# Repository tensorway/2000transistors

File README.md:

# 2000 MOSFET processor

The project is made in Kicad. If you want to learn more about it visit [howcpuworks.com](howcpuworks.com).

## Conventions
- all transistors on a board point into the same direction (or 2 perpendicular ones if needed)
- all leds point into the same direction
- 1k resistors are labeled with white rectangle, 1M with empty one (only violation is in the Clock board and two voltage divider resistors in LCD board)
- "*" means high significance bits
- "+" means positive 5V

## Tips
- you dont need to use extra usb for the power, powering through arduino is enough
- Adder is made out of 2 smaller 6 bit adders, this means that you do not have to solder one bit (6+6=12 != 11)
- instruction register needs only 5bits which means you do not have to solder upper 6 bits (all registers are the same board to lower costs)
- when soldering
  - first put resistors
  - than transistors from the top left (top right if left handed)
  - leds and pin headers last

## Important
- to lower costs all registers have the same board, but TMP and IR registers do not have input and output connected to the bus, this means you have to connect it on other registers
- You need to find the voltage that works for your LCD contrast and put those resistors

## Components
- 2N7000 MOSFETs
- BC547 (BJT) only 4 for the astable
- 1000 ohm registers for leds
- 1M ohm for logic

## Bugs

While I could fix the bugs I do not want to check is everything working again because I would need to solder things again. This is why I list them, so you can either fix them yourselves before or after soldering (I did after).
Some bugs are just layout bugs, which means you need to be aware of them but not necessarily fix them.

Micromemory:
- shuffled by row led, select and switches - layout bug
- 0th line not connected to rest

Micromemory stepper:
- shuffeled LED state order - layout bug
- add delay from clock to it (for example RC)
   
Keyboard
- same signals for simetrical (with respect to keyboard diagonal) switches
  - effectively half the number of switches
- 1 bit not connected
  
Flags
- second to last carry and last carry labels mixed - layout bug
- flags selector selects 0 always

Clock
- manual clock does not have a debouncer

ALU
- add OR between ALU decoded ops and give Adder the output

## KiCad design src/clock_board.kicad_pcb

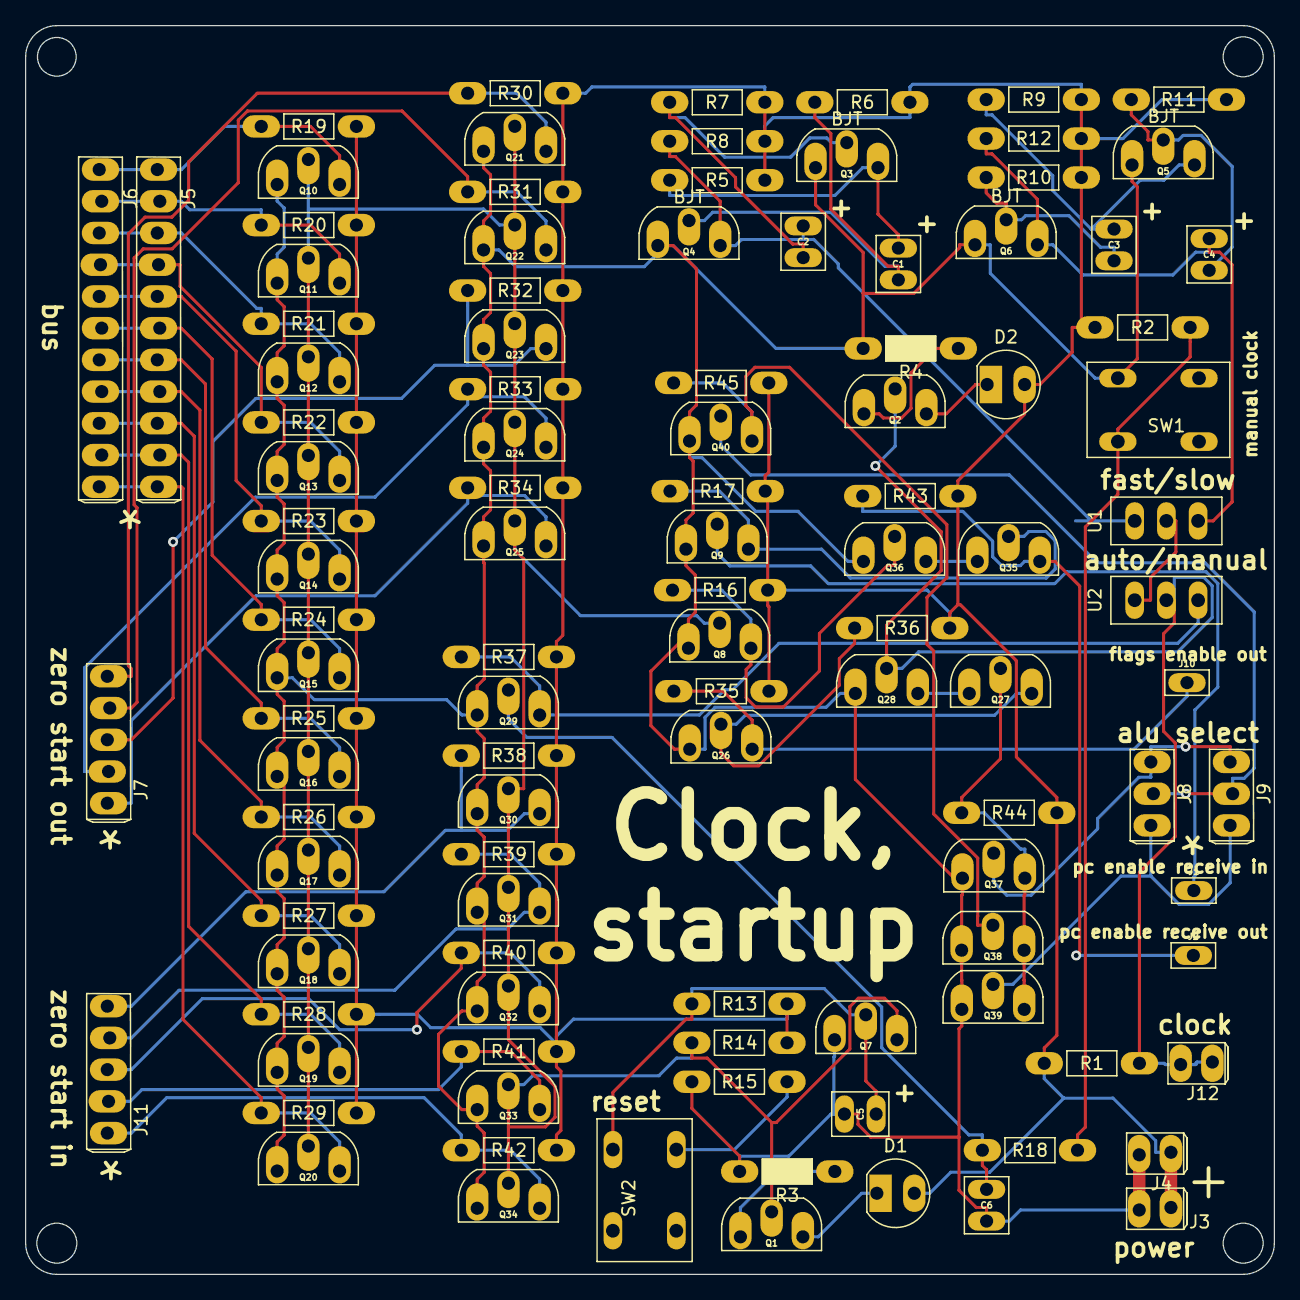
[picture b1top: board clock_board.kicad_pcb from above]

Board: 2 copper layers, 100.0 x 100.0 mm, 109 parts (0 on the bottom side), 56 nets.

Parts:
C1, C2, C3, C4: CP; capacitor
C5, C6: C; capacitor
D1, D2: LED; led_5mm_tight
J1, J2: Conn_01x01_Male; 1pin
J3, J4, J12: Conn_01x02_Male; 2pin_tight
J5, J6: Conn_01x11_Male; 11pin_tight
J7, J11: Conn_01x05_Male; 5pin_tight
J8, J9: alu_sel; 3pin_tight
J10: flags_enable_out; 1pin
Q1, Q2, Q7, Q8, Q9, Q10, Q11, Q12, Q13, Q14, Q15, Q16, Q17, Q18, Q19, Q20, Q21, Q22, Q23, Q24, Q25, Q26, Q27, Q28, Q29, Q30, Q31, Q32, Q33, Q34, Q35, Q36, Q37, Q38, Q39, Q40: 2N7000; 2n7000_tight
Q3, Q4, Q5, Q6: 2N2219; bjt
R1, R2, R5, R6, R7, R8, R9, R10, R11, R12, R13, R14, R15, R16, R17, R18, R19, R20, R21, R22, R23, R24, R25, R26, R27, R28, R29, R30, R31, R32, R33, R34, R35, R36, R37, R38, R39, R40, R41, R42, R43, R44, R45: R; resistor_tight
R3, R4: R; resistor_led_tight
SW1, SW2: SW_Push_Dual; push_button
U1, U2: slide_switch

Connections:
+5V: D1.2, D2.2, J3.1, J4.1, R1.1, R2.1, R5.1, R6.1, R7.1, R8.1, R9.1, R10.1, R11.1, R12.1, R13.1, R14.1, R16.1, R17.1, R19.1, R20.1, R21.1, R22.1, R23.1, R24.1, R25.1, R26.1, R27.1, R28.1, R29.1, R30.1, R31.1, R32.1, R33.1, R34.1, R35.1, R36.1, R37.1, R38.1, R39.1, R40.1, R41.1, R42.1, R43.1, R44.1, R45.1
/Sheet63E28E4F/a: J5.11, J6.11, Q20.3, R29.2
/Sheet63E28E4F/ain: Q1.2, Q7.3, Q8.2, Q10.2, Q11.2, Q12.2, Q13.2, Q14.2, Q15.2, Q16.2, Q17.2, Q18.2, Q19.2, Q20.2, Q21.2, Q22.2, Q23.2, Q24.2, Q25.2, Q30.2, Q31.2, Q32.2, Q33.2, Q34.2, R14.2
/Sheet63E28E4F/b: J5.10, J6.10, Q19.3, R28.2
/Sheet63E28E4F/c: J5.9, J6.9, Q18.3, R27.2
/Sheet63E28E4F/d: J5.8, J6.8, Q17.3, R26.2
/Sheet63E28E4F/e: J5.7, J6.7, Q16.3, R25.2
/Sheet63E28E4F/f: J5.6, J6.6, Q15.3, R24.2
/Sheet63E28E4F/g: J5.5, J6.5, Q14.3, R23.2
/Sheet63E28E4F/h: J5.4, J6.4, Q13.3, R22.2
/Sheet63E28E4F/i: J5.3, J6.3, Q12.3, R21.2
/Sheet63E28E4F/j: J5.2, J6.2, Q11.3, R20.2
/Sheet63E28E4F/k: J5.1, J6.1, Q10.3, R19.2
/Sheet63E92C8A/a: J7.1, Q21.3, R30.2
/Sheet63E92C8A/b: J7.2, Q22.3, R31.2
/Sheet63E92C8A/c: J7.3, Q23.3, R32.2
/Sheet63E92C8A/d: J7.4, Q24.3, R33.2
/Sheet63E92C8A/e: J7.5, Q25.3, R34.2
/Sheet63F3BCE0/a: J8.1, J9.1, Q37.2
/Sheet63F3BCE0/b: Q38.2, Q40.3, R45.2
/Sheet63F3BCE0/c: J8.3, J9.3, Q39.2
/Sheet63F170A3/in: R2.2, R18.1, SW1.2
/fast_clck/out: C2.1, Q4.3, R8.2, U1.a
/sheet63E014FB/a: Q27.2, Q37.3, Q38.3, Q39.3, R44.2
/sheet63E014FB/b: J12.1, J12.2, Q2.2, Q28.2, R1.2, U2.common
/sheet63E014FC/in: J8.2, J9.2, Q40.2
/sheet63E741C0/a: Q9.3, Q35.2, R17.2
/sheet63E741C0/b: Q8.3, Q36.2, R16.2
/sheet63E741C0/out: J2.1, Q35.3, R43.2
/sheet63E741C1/in: J1.1, Q9.2
/sheet63E4453A/a: J11.1, Q30.3, R38.2
/sheet63E4453A/b: J11.2, Q31.3, R39.2
/sheet63E4453A/c: J11.3, Q32.3, R40.2
/sheet63E4453A/d: J11.4, Q33.3, R41.2
/sheet63E4453A/e: J11.5, Q34.3, R42.2
/sheet63F0C454/in: Q26.2, Q27.3, R36.2
/sheet63F0C454/out: J10.1, Q26.3, R35.2
/sheet63F5D8BA/in: C6.1, Q29.2, R18.2
/sheet63F5D8BA/out: Q29.3, R37.2, U2.b
/slow_clck/out: C4.1, Q6.3, R12.2, U1.b
GND: C5.2, C6.2, J3.2, J4.2, Q3.1, Q4.1, Q5.1, Q6.1, Q7.1, Q8.1, Q9.1, Q10.1, Q11.1, Q12.1, Q13.1, Q14.1, Q15.1, Q16.1, Q17.1, Q18.1, Q19.1, Q20.1, Q21.1, Q22.1, Q23.1, Q24.1, Q25.1, Q26.1, Q28.1, Q29.1, Q30.1, Q31.1, Q32.1, Q33.1, Q34.1, Q36.1, Q37.1, Q38.1, Q39.1, Q40.1, R3.2, R4.2, R15.2, SW1.1
unnamed: C1.1, Q3.3, R5.2
unnamed: C1.2, Q4.2, R6.2
unnamed: C2.2, Q3.2, R7.2
unnamed: C3.1, Q5.3, R9.2
unnamed: C3.2, Q6.2, R10.2
unnamed: C4.2, Q5.2, R11.2
unnamed: C5.1, Q7.2, R13.2, SW2.2
unnamed: D1.1, Q1.3
unnamed: D2.1, Q2.3
unnamed: Q1.1, R3.1
unnamed: Q2.1, R4.1
unnamed: Q27.1, Q28.3
unnamed: Q35.1, Q36.3
unnamed: R15.1, SW2.1
unnamed: U1.common, U2.a

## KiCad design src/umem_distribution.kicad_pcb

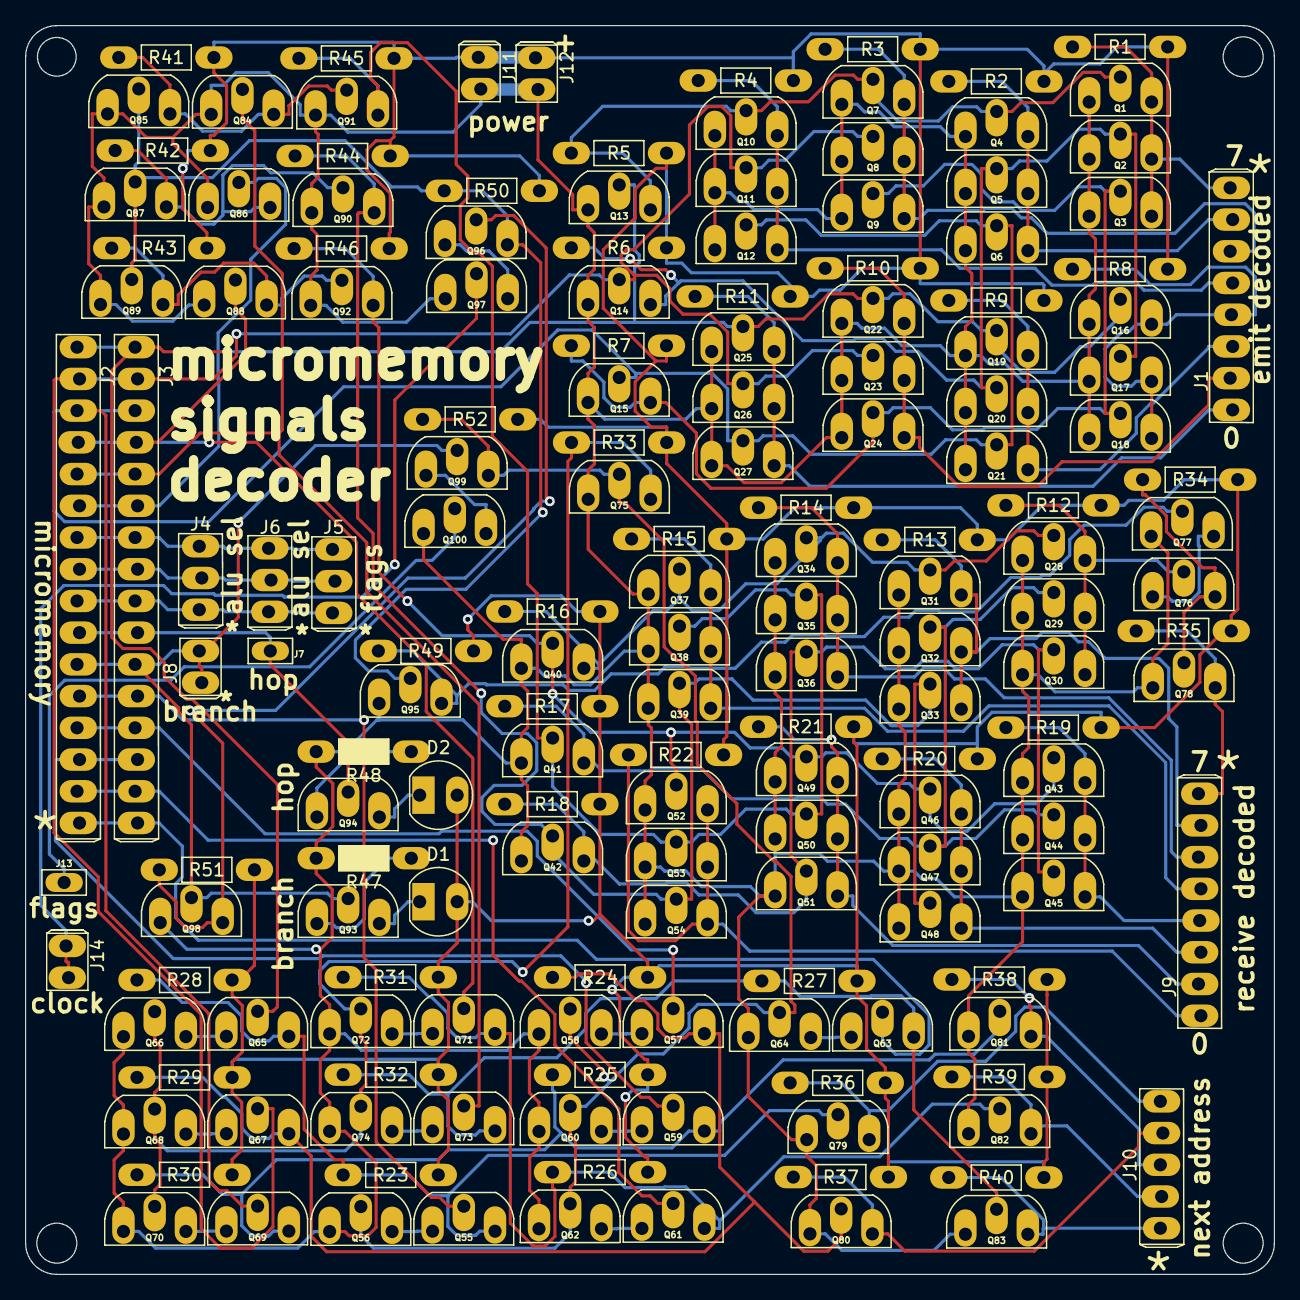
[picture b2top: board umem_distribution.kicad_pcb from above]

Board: 2 copper layers, 100.0 x 100.0 mm, 168 parts (0 on the bottom side), 82 nets.

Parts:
D1, D2: LED; led_5mm_tight
J1: emit_signals; 8pin_tight
J2, J3: Conn_01x16_Male; 16pin_tight
J4: alu_sel; 3pin_tight
J5: flags; 3pin_tight
J6: alu sel; 3pin_tight
J7: hop; 1pin
J8: branch; 2pin_tight
J9: receive_signals; 8pin_tight
J10: Conn_01x05_Male; 5pin_tight
J11, J12: Conn_01x02_Male; 2pin_tight
J13: flags; 1pin
J14: clck; 2pin_tight
Q1, Q2, Q3, Q4, Q5, Q6, Q7, Q8, Q9, Q10, Q11, Q12, Q13, Q14, Q15, Q16, Q17, Q18, Q19, Q20, Q21, Q22, Q23, Q24, Q25, Q26, Q27, Q28, Q29, Q30, Q31, Q32, Q33, Q34, Q35, Q36, Q37, Q38, Q39, Q40, Q41, Q42, Q43, Q44, Q45, Q46, Q47, Q48, Q49, Q50, Q51, Q52, Q53, Q54, Q55, Q56, Q57, Q58, Q59, Q60, Q61, Q62, Q63, Q64, Q65, Q66, Q67, Q68, Q69, Q70, Q71, Q72, Q73, Q74, Q75, Q76, Q77, Q78, Q79, Q80, Q81, Q82, Q83, Q84, Q85, Q86, Q87, Q88, Q89, Q90, Q91, Q92, Q93, Q94, Q95, Q96, Q97, Q98, Q99, Q100: 2N7000; 2n7000_tight
R1, R2, R3, R4, R5, R6, R7, R8, R9, R10, R11, R12, R13, R14, R15, R16, R17, R18, R19, R20, R21, R22, R23, R24, R25, R26, R27, R28, R29, R30, R31, R32, R33, R34, R35, R36, R37, R38, R39, R40, R41, R42, R43, R44, R45, R46, R49, R50, R51, R52: R; resistor_tight
R47, R48: R; resistor_led_tight

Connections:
+5V: D1.2, D2.2, J11.1, J12.1, R1.1, R2.1, R3.1, R4.1, R5.1, R6.1, R7.1, R8.1, R9.1, R10.1, R11.1, R12.1, R13.1, R14.1, R15.1, R16.1, R17.1, R18.1, R19.1, R20.1, R21.1, R22.1, R23.1, R24.1, R25.1, R26.1, R27.1, R28.1, R29.1, R30.1, R31.1, R32.1, R33.1, R34.1, R35.1, R36.1, R37.1, R38.1, R39.1, R40.1, R41.1, R42.1, R43.1, R44.1, R45.1, R46.1, R49.1, R50.1, R51.1, R52.1
/Sheet63E6B315/a: Q40.2, Q43.2, Q46.2, Q49.2, Q52.2, Q92.3, R46.2
/Sheet63E6B315/b: Q35.2, Q38.2, Q41.2, Q50.2, Q53.2, Q91.3, R45.2
/Sheet63E6B315/c: Q33.2, Q39.2, Q42.2, Q48.2, Q54.2, Q90.3, R44.2
/Sheet63E6B315/cin: J2.6, J3.6, Q86.2
/Sheet63E6B315/enable: Q85.2, Q87.2, Q89.2, Q95.2, Q96.3, R50.2
/Sheet63E6B315/sheet63E6BA43/in: Q86.3, Q87.3, Q90.2, R42.2
/Sheet63E6B315/sheet63E6BA44/in: Q84.3, Q85.3, Q91.2, R41.2
/Sheet63E6B315/sheet63E6BA45/in: Q88.3, Q89.3, Q92.2, R43.2
/Sheet63E20833/a: J10.1, Q79.3, R36.2
/Sheet63E20833/ain: Q55.3, Q65.3, Q79.2, R23.2, R28.2
/Sheet63E20833/b: J10.2, Q80.3, R37.2
/Sheet63E20833/bin: Q57.3, Q67.3, Q80.2, R24.2, R29.2
/Sheet63E20833/c: J10.3, Q81.3, R38.2
/Sheet63E20833/cin: Q59.3, Q69.3, Q81.2, R25.2, R30.2
/Sheet63E20833/d: J10.4, Q82.3, R39.2
/Sheet63E20833/din: Q61.3, Q71.3, Q82.2, R26.2, R31.2
/Sheet63E20833/e: J10.5, Q83.3, R40.2
/Sheet63E20833/ein: Q63.3, Q73.3, Q83.2, R27.2, R32.2
/Sheet6491BA02/a: J2.11, J3.11, J8.1, J8.2, Q93.2, Q98.2, Q99.2
/Sheet6491BA02/b: J13.1, Q100.2
/Sheet6486733A/a: Q96.2, Q98.3, R51.2
/Sheet6486733A/b: J14.1, J14.2, Q97.2
/emit/Sheet63BAB2B1/a: Q1.2, Q4.2, Q7.2, Q10.2, Q13.3, R5.2
/emit/Sheet63BAB2B1/b: Q2.2, Q5.2, Q14.3, Q17.2, Q20.2, R6.2
/emit/Sheet63BAB2B1/c: Q3.2, Q9.2, Q15.3, Q18.2, Q24.2, R7.2
/emit/a: J1.1, Q25.3, Q26.3, Q27.3, R11.2
/emit/b: J1.2, Q22.3, Q23.3, Q24.3, R10.2
/emit/c: J1.3, Q19.3, Q20.3, Q21.3, R9.2
/emit/d: J1.4, Q16.3, Q17.3, Q18.3, R8.2
/emit/e: J1.5, Q10.3, Q11.3, Q12.3, R4.2
/emit/f: J1.6, Q7.3, Q8.3, Q9.3, R3.2
/emit/g: J1.7, Q4.3, Q5.3, Q6.3, R2.2
/emit/h: J1.8, Q1.3, Q2.3, Q3.3, R1.2
/hop/in: J2.10, J3.10, J7.1, Q94.2
/receive/Sheet63BAB2B1/a: Q28.2, Q31.2, Q34.2, Q37.2, Q40.3, R16.2
/receive/Sheet63BAB2B1/b: Q29.2, Q32.2, Q41.3, Q44.2, Q47.2, R17.2
/receive/Sheet63BAB2B1/c: Q30.2, Q36.2, Q42.3, Q45.2, Q51.2, R18.2
/receive/a: J9.1, Q52.3, Q53.3, Q54.3, R22.2
/receive/b: J9.2, Q49.3, Q50.3, Q51.3, R21.2
/receive/c: J9.3, Q46.3, Q47.3, Q48.3, R20.2
/receive/d: J9.4, Q43.3, Q44.3, Q45.3, R19.2
/receive/e: J9.5, Q37.3, Q38.3, Q39.3, R15.2
/receive/f: J9.6, Q34.3, Q35.3, Q36.3, R14.2
/receive/g: J9.7, Q31.3, Q32.3, Q33.3, R13.2
/sheet63E5B14C/a: J2.13, J3.13, Q57.2
/sheet63E5C954/a: J2.14, J3.14, Q59.2
/sheet63E5E118/a: J2.15, J3.15, Q61.2
/sheet63E5F8EC/a: J2.16, J3.16, Q63.2
/sheet63E6165A/a: J2.1, J3.1, Q13.2, Q16.2, Q19.2, Q22.2, Q25.2, Q65.2
/sheet63E6165A/b: Q66.2, Q68.2, Q70.2, Q72.2, Q74.2, Q75.3, R33.2
/sheet63E6165B/a: J2.2, J3.2, Q8.2, Q11.2, Q14.2, Q23.2, Q26.2, Q67.2
/sheet63E6165C/a: J2.3, J3.3, Q6.2, Q12.2, Q15.2, Q21.2, Q27.2, Q69.2
/sheet63E6165D/a: J2.4, J3.4, Q71.2, Q88.2
/sheet63E6165E/a: J2.5, J3.5, Q73.2, Q84.2
/sheet63E59739/a: J2.12, J3.12, Q55.2
/sheet63E59739/b: Q56.2, Q58.2, Q60.2, Q62.2, Q64.2, Q75.2, Q99.3, R52.2
/sheet640275C6/a: Q28.3, Q29.3, Q30.3, Q76.2, R12.2
/sheet640275C6/b: Q77.2, Q95.3, R49.2
/sheet640275C7/in: Q76.3, Q78.2, R34.2
/sheet640275C7/out: J9.8, Q78.3, R35.2
GND: J11.2, J12.2, Q1.1, Q2.1, Q3.1, Q4.1, Q5.1, Q6.1, Q7.1, Q8.1, Q9.1, Q10.1, Q11.1, Q12.1, Q13.1, Q14.1, Q15.1, Q16.1, Q17.1, Q18.1, Q19.1, Q20.1, Q21.1, Q22.1, Q23.1, Q24.1, Q25.1, Q26.1, Q27.1, Q28.1, Q29.1, Q30.1, Q31.1, Q32.1, Q33.1, Q34.1, Q35.1, Q36.1, Q37.1, Q38.1, Q39.1, Q40.1, Q41.1, Q42.1, Q43.1, Q44.1, Q45.1, Q46.1, Q47.1, Q48.1, Q49.1, Q50.1, Q51.1, Q52.1, Q53.1, Q54.1, Q56.1, Q58.1, Q60.1, Q62.1, Q64.1, Q66.1, Q68.1, Q70.1, Q72.1, Q74.1, Q75.1, Q77.1, Q78.1, Q79.1, Q80.1, Q81.1, Q82.1, Q83.1, Q84.1, Q85.1, Q86.1, Q87.1, Q88.1, Q89.1, Q90.1, Q91.1, Q92.1, Q95.1, Q97.1, Q98.1, Q100.1, R47.2, R48.2
unnamed: D1.1, Q93.3
unnamed: D2.1, Q94.3
unnamed: J2.7, J3.7, J4.1, J5.1, J6.1
unnamed: J2.8, J3.8, J4.2, J5.2, J6.2
unnamed: J2.9, J3.9, J4.3, J5.3, J6.3
unnamed: Q55.1, Q56.3
unnamed: Q57.1, Q58.3
unnamed: Q59.1, Q60.3
unnamed: Q61.1, Q62.3
unnamed: Q63.1, Q64.3
unnamed: Q65.1, Q66.3
unnamed: Q67.1, Q68.3
unnamed: Q69.1, Q70.3
unnamed: Q71.1, Q72.3
unnamed: Q73.1, Q74.3
unnamed: Q76.1, Q77.3
unnamed: Q93.1, R47.1
unnamed: Q94.1, R48.1
unnamed: Q96.1, Q97.3
unnamed: Q99.1, Q100.3

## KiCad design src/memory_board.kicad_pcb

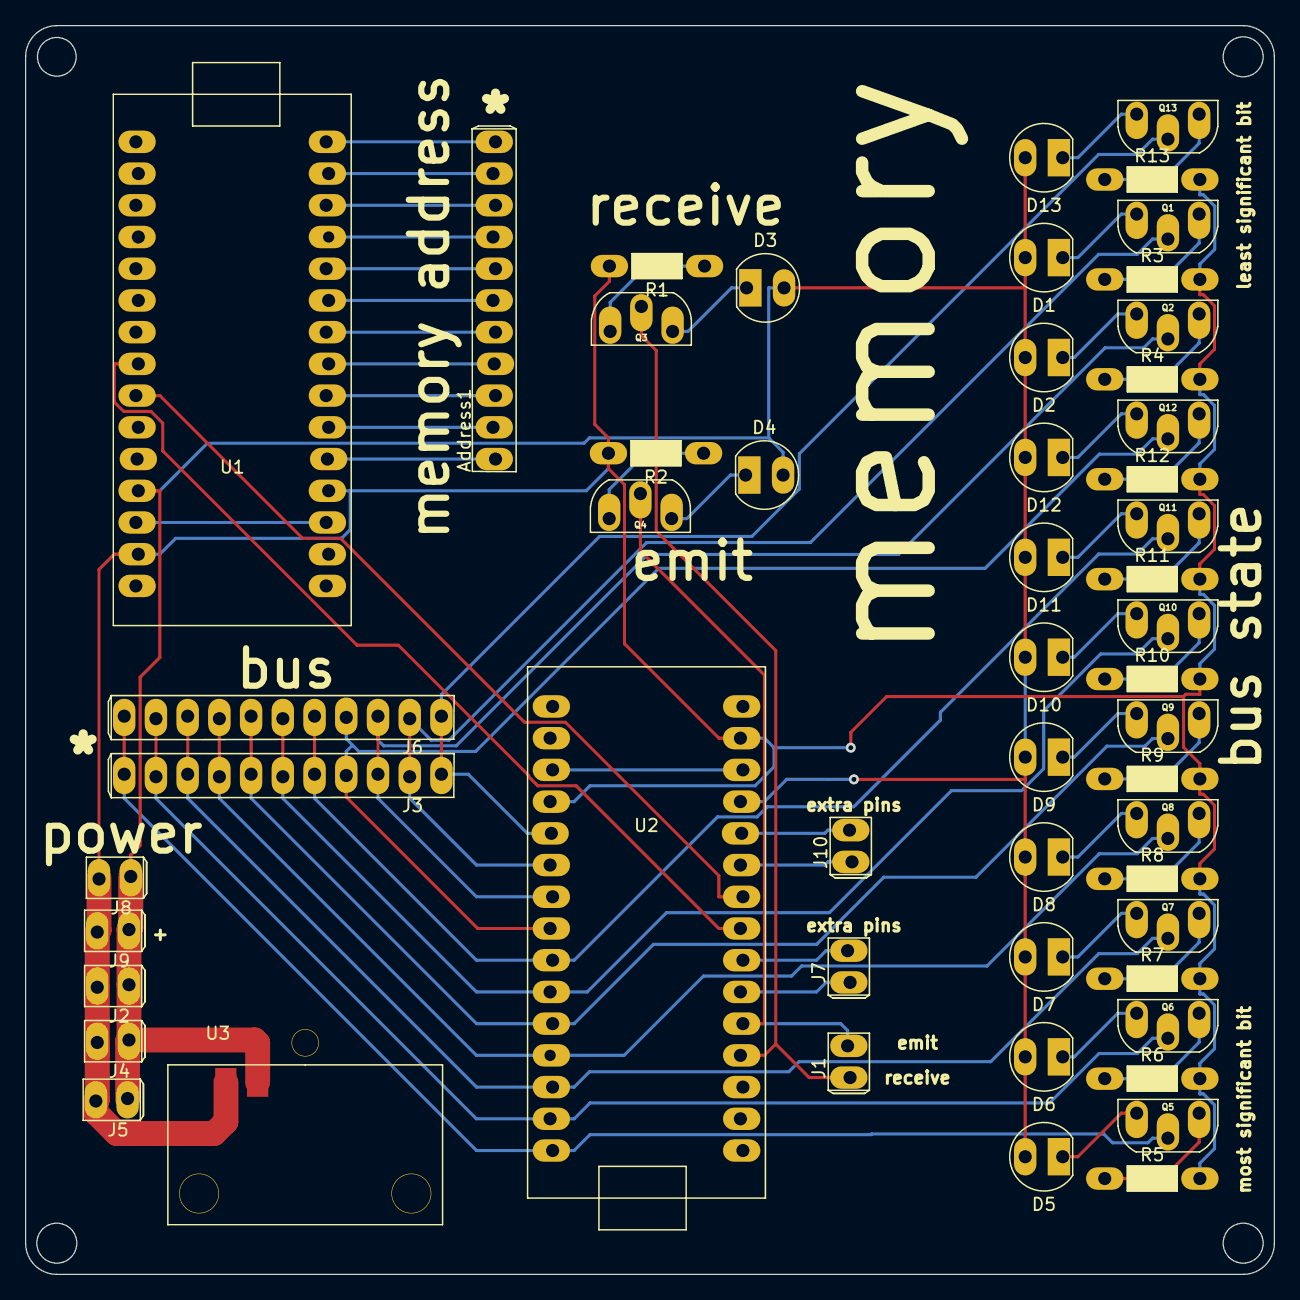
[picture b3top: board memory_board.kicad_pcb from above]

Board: 2 copper layers, 100.0 x 100.0 mm, 53 parts (0 on the bottom side), 58 nets.

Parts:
Address1: Conn_01x11_Male; 11pin_tight
D1, D2, D3, D4, D5, D6, D7, D8, D9, D10, D11, D12, D13: LED; led_5mm_tight
J1, J2, J4, J5, J8, J9: Conn_01x02_Male; 2pin_tight
J3, J6: Conn_01x11_Male; 11pin_tight
J7: emergency_pins_1; 2pin_tight
J10: emergency_pins_2; 2pin_tight
Q1, Q2, Q3, Q4, Q5, Q6, Q7, Q8, Q9, Q10, Q11, Q12, Q13: 2N7000; 2n7000_tight
R1, R2, R3, R4, R5, R6, R7, R8, R9, R10, R11, R12, R13: R; resistor_led_tight
U1, U2: arduino_nano
U3: usb_c_power

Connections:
+5V: D1.2, D2.2, D3.2, D4.2, D5.2, D6.2, D7.2, D8.2, D9.2, D10.2, D11.2, D12.2, D13.2, J2.1, J4.1, J5.1, J8.1, J9.1, U1.5V, U2.5V, U3.gnd
/Sheet63DB05CB/in: J1.1, Q3.2, U2.a0
/sheet63DB2CAC/in: J1.2, Q4.2, U2.a1
/sheet63DBD05A/in: J3.11, J6.11, Q5.2, U2.d12
/sheet63DBD05B/in: J3.10, J6.10, Q6.2, U2.d11
/sheet63DC1151/in: J3.9, J6.9, Q7.2, U2.d10
/sheet63DC1152/in: J3.8, J6.8, Q8.2, U2.d9
/sheet63DCF52A/in: J3.7, J6.7, Q9.2, U2.d8
/sheet63DCF52B/in: J3.6, J6.6, Q10.2, U2.d7
/sheet63DCF52C/in: J3.5, J6.5, Q11.2, U2.d6
/sheet63DCF52D/in: J3.4, J6.4, Q12.2, U2.d5
/sheet63DE894A/in: J3.3, J6.3, Q2.2, U2.d4
/sheet63DE894B/in: J3.2, J6.2, Q1.2, U2.d3
/sheet63DE894C/in: J3.1, J6.1, Q13.2, U2.d2
GND: J2.2, J4.2, J5.2, J8.2, J9.2, R1.2, R2.2, R3.2, R4.2, R5.2, R6.2, R7.2, R8.2, R9.2, R10.2, R11.2, R12.2, R13.2, U1.GND, U2.GND, U3.5v
unnamed: Address1.1, U1.d2
unnamed: Address1.2, U1.d3
unnamed: Address1.3, U1.d4
unnamed: Address1.4, U1.d5
unnamed: Address1.5, U1.d6
unnamed: Address1.6, U1.d7
unnamed: Address1.7, U1.d8
unnamed: Address1.8, U1.d9
unnamed: Address1.9, U1.d10
unnamed: Address1.10, U1.d11
unnamed: Address1.11, U1.d12
unnamed: D1.1, Q1.3
unnamed: D2.1, Q2.3
unnamed: D3.1, Q3.3
unnamed: D4.1, Q4.3
unnamed: D5.1, Q5.3
unnamed: D6.1, Q6.3
unnamed: D7.1, Q7.3
unnamed: D8.1, Q8.3
unnamed: D9.1, Q9.3
unnamed: D10.1, Q10.3
unnamed: D11.1, Q11.3
unnamed: D12.1, Q12.3
unnamed: D13.1, Q13.3
unnamed: J7.1, U2.a2
unnamed: J7.2, U2.a3
unnamed: J10.1, U2.a6
unnamed: J10.2, U2.a7
unnamed: Q1.1, R3.1
unnamed: Q2.1, R4.1
unnamed: Q3.1, R1.1
unnamed: Q4.1, R2.1
unnamed: Q5.1, R5.1
unnamed: Q6.1, R6.1
unnamed: Q7.1, R7.1
unnamed: Q8.1, R8.1
unnamed: Q9.1, R9.1
unnamed: Q10.1, R10.1
unnamed: Q11.1, R11.1
unnamed: Q12.1, R12.1
unnamed: Q13.1, R13.1
unnamed: U1.SCL, U2.SCL
unnamed: U1.SDA, U2.SDA

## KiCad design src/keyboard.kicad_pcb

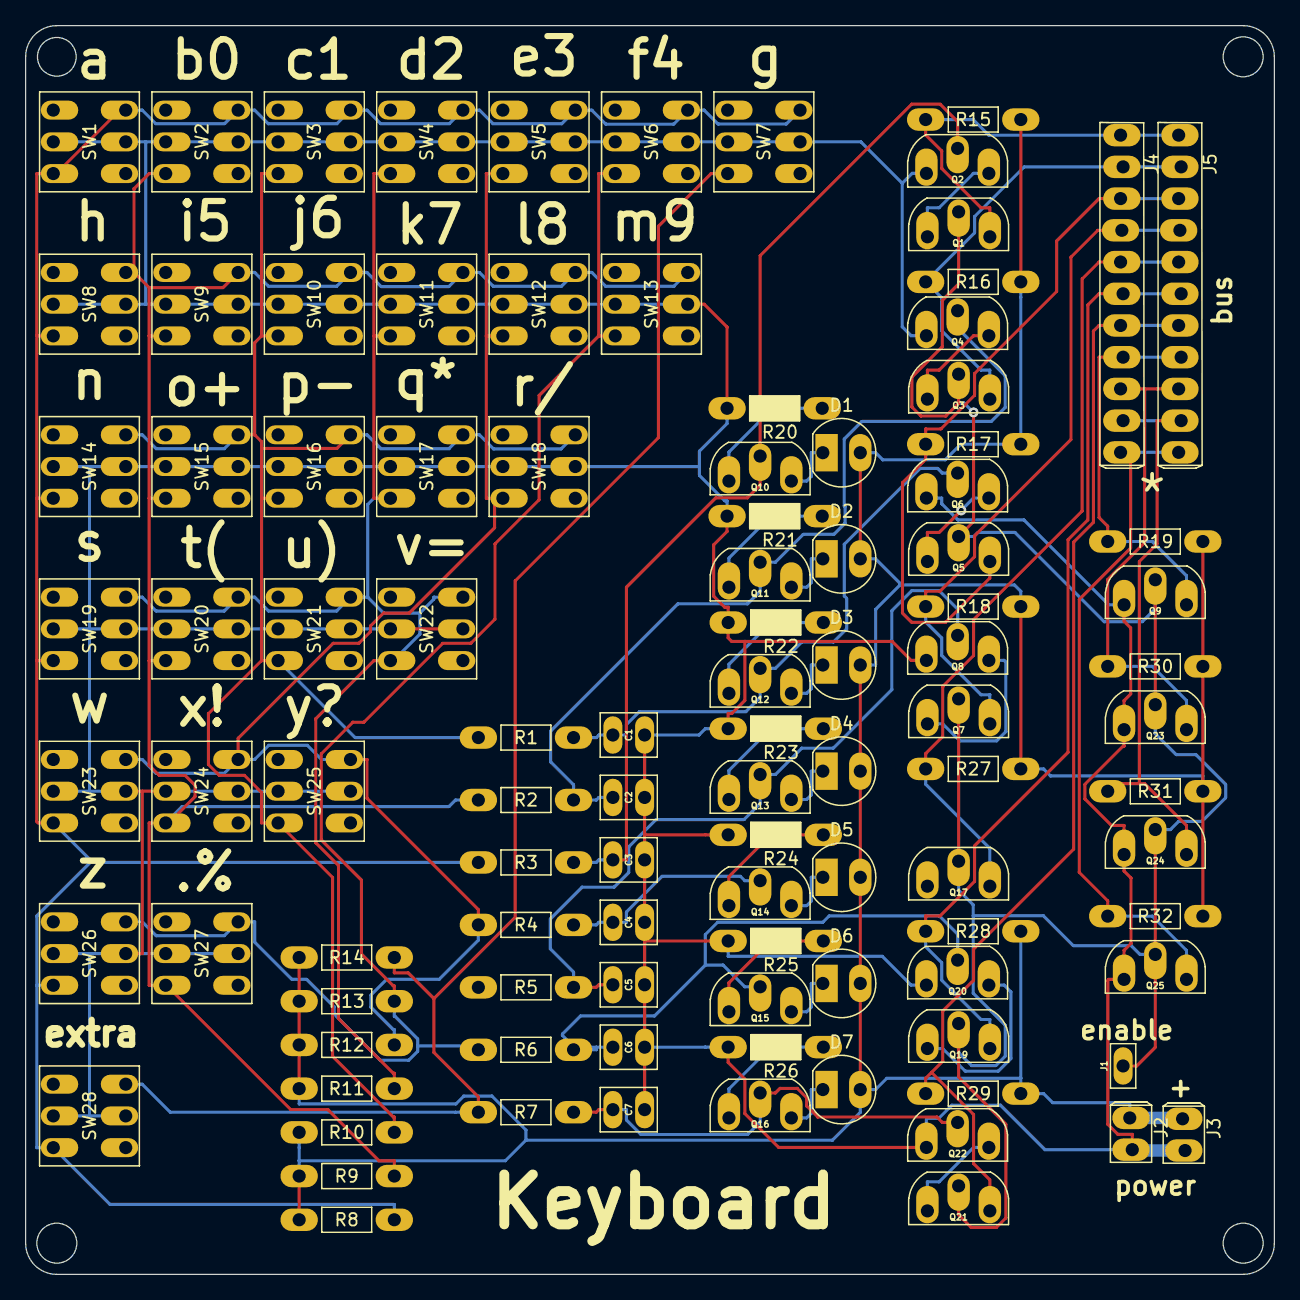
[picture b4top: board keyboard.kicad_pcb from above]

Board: 2 copper layers, 100.0 x 100.0 mm, 103 parts (0 on the bottom side), 48 nets.

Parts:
C1, C2, C3, C4, C5, C6, C7: C; capacitor
D1, D2, D3, D4, D5, D6, D7: LED; led_5mm_tight
J1: Conn_01x01_Male; 1pin
J2, J3: Conn_01x02_Male; 2pin_tight
J4, J5: Conn_01x11_Male; 11pin_tight
Q1, Q2, Q3, Q4, Q5, Q6, Q7, Q8, Q9, Q10, Q11, Q12, Q13, Q14, Q15, Q16, Q17, Q19, Q20, Q21, Q22, Q23, Q24, Q25: 2N7000; 2n7000_tight
R1, R2, R3, R4, R5, R6, R7, R8, R9, R10, R11, R12, R13, R14, R15, R16, R17, R18, R19, R27, R28, R29, R30, R31, R32: R; resistor_tight
R20, R21, R22, R23, R24, R25, R26: R; resistor_led_tight
SW1, SW2, SW3, SW4, SW5, SW6, SW7, SW8, SW9, SW10, SW11, SW12, SW13, SW14, SW15, SW16, SW17, SW18, SW19, SW20, SW21, SW22, SW23, SW24, SW25, SW26, SW27, SW28: SW_Push_DPDT; dpdt_switch

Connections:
+5V: D1.2, D2.2, D3.2, D4.2, D5.2, D6.2, D7.2, J2.1, J3.1, R8.1, R9.1, R10.1, R11.1, R12.1, R13.1, R14.1, R15.1, R16.1, R17.1, R18.1, R19.1, R27.1, R28.1, R29.1, R30.1, R31.1, R32.1
/Sheet63C33C3A/a: J1.1, Q1.2, Q3.2, Q5.2, Q7.2, Q9.2, Q17.2, Q19.2, Q21.2, Q23.2, Q24.2, Q25.2
/Sheet63C33C3A/out: J4.1, J5.1, Q1.3, R15.2
/Sheet63C1613A/a: C3.1, Q2.2, Q10.2, R3.2
/Sheet63C1613A/b: C2.1, Q4.2, Q11.2, R2.2
/Sheet63C1613A/sheet63C18FE1/a: R3.1, R8.2, SW1.2, SW1.5, SW2.2, SW3.2, SW4.2, SW5.2, SW6.2, SW7.2, SW8.5, SW14.5, SW19.5, SW23.5, SW26.5, SW28.5
/Sheet63C1613A/sheet63C18FE1/b: R2.1, R9.2, SW2.5, SW8.2, SW9.2, SW9.5, SW10.2, SW11.2, SW12.2, SW13.2, SW15.5, SW20.5, SW24.5, SW27.5
/Sheet63C1613A/sheet63C18FE1/c: R1.1, R10.2, SW3.5, SW10.5, SW14.2, SW15.2, SW16.2, SW16.5, SW17.2, SW18.2, SW21.5, SW25.5
/Sheet63C1613A/sheet63C18FE1/d: R11.2, SW4.5, SW11.5, SW17.5, SW19.2, SW20.2, SW21.2, SW22.2, SW22.5
/Sheet63C1613A/sheet63C18FE1/e: R4.1, R12.2, SW5.5, SW12.5, SW18.5, SW23.2, SW24.2, SW25.2
/Sheet63C1613A/sheet63C18FE1/f: R6.1, R13.2, SW6.5, SW13.5, SW26.2, SW27.2
/Sheet63C1613A/sheet63C18FE1/g: R7.1, R14.2, SW7.5, SW28.2
/Sheet63CC3F40/out: J4.8, J5.8, Q9.3, R19.2
/sheet63C34C32/b: C7.1, Q16.2, Q22.2, R7.2
/sheet63C34C32/out: J4.7, J5.7, Q21.3, R29.2
/sheet63C342CE/out: J4.2, J5.2, Q3.3, R16.2
/sheet63C343CC/b: C1.1, Q6.2, Q12.2, R1.2
/sheet63C343CC/out: J4.3, J5.3, Q5.3, R17.2
/sheet63C348D6/b: C5.1, Q8.2, Q13.2, R5.2
/sheet63C348D6/out: J4.4, J5.4, Q7.3, R18.2
/sheet63C348D7/b: C4.1, Q14.2, R4.2
/sheet63C348D7/out: J4.5, J5.5, Q17.3, R27.2
/sheet63C348D8/b: C6.1, Q15.2, Q20.2, R6.2
/sheet63C348D8/out: J4.6, J5.6, Q19.3, R28.2
/sheet63E7D33C/out: J4.11, J5.11, Q25.3, R32.2
/sheet63E76C8C/out: J4.9, J5.9, Q23.3, R30.2
/sheet63E79FE1/out: J4.10, J5.10, Q24.3, R31.2
GND: C1.2, C2.2, C3.2, C4.2, C5.2, C6.2, C7.2, J2.2, J3.2, Q2.1, Q4.1, Q6.1, Q8.1, Q9.1, Q20.1, Q22.1, Q23.1, Q24.1, Q25.1, R20.2, R21.2, R22.2, R23.2, R24.2, R25.2, R26.2, SW1.3, SW1.6, SW2.3, SW2.6, SW3.3, SW3.6, SW4.3, SW4.6, SW5.3, SW5.6, SW6.3, SW6.6, SW7.3, SW7.6, SW8.3, SW8.6, SW9.3, SW9.6, SW10.3, SW10.6, SW11.3, SW11.6, SW12.3, SW12.6, SW13.3, SW13.6, SW14.3, SW14.6, SW15.3, SW15.6, SW16.3, SW16.6, SW17.3, SW17.6, SW18.3, SW18.6, SW19.3, SW19.6, SW20.3, SW20.6, SW21.3, SW21.6, SW22.3, SW22.6, SW23.3, SW23.6, SW24.3, SW24.6, SW25.3, SW25.6, SW26.3, SW26.6, SW27.3, SW27.6, SW28.3, SW28.6
unnamed: D1.1, Q10.3
unnamed: D2.1, Q11.3
unnamed: D3.1, Q12.3
unnamed: D4.1, Q13.3
unnamed: D5.1, Q14.3
unnamed: D6.1, Q15.3
unnamed: D7.1, Q16.3
unnamed: Q1.1, Q2.3
unnamed: Q3.1, Q4.3
unnamed: Q5.1, Q6.3
unnamed: Q7.1, Q8.3
unnamed: Q10.1, R20.1
unnamed: Q11.1, R21.1
unnamed: Q12.1, R22.1
unnamed: Q13.1, R23.1
unnamed: Q14.1, R24.1
unnamed: Q15.1, R25.1
unnamed: Q16.1, R26.1
unnamed: Q19.1, Q20.3
unnamed: Q21.1, Q22.3

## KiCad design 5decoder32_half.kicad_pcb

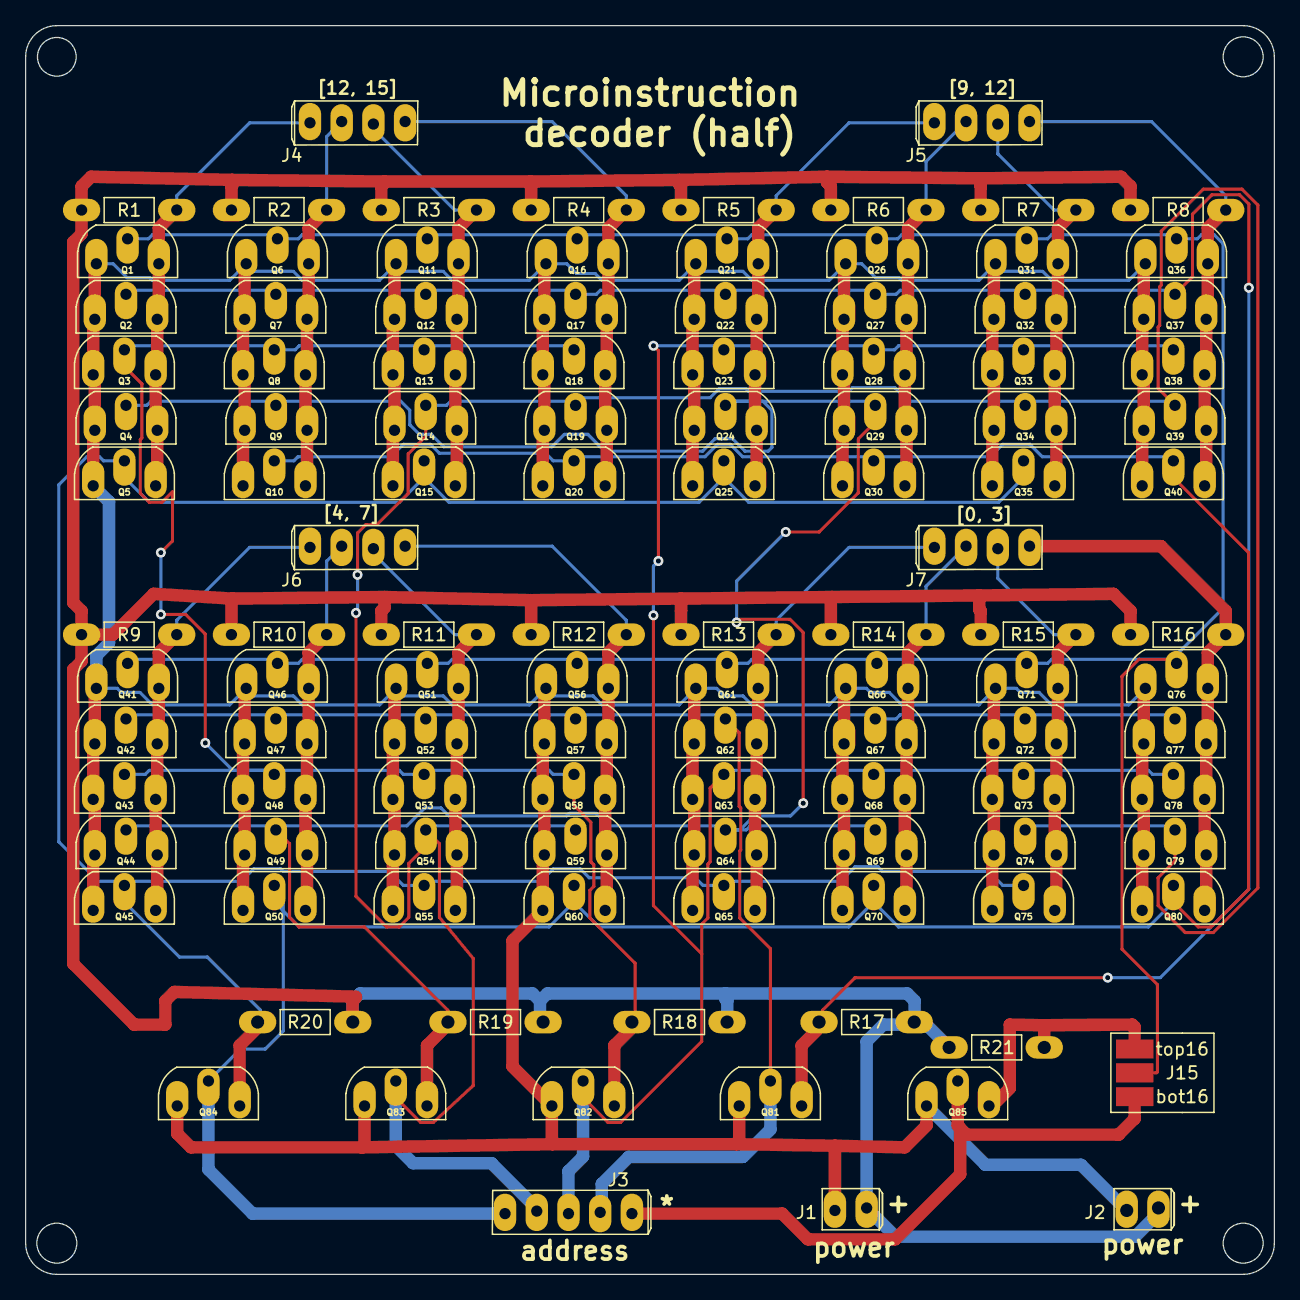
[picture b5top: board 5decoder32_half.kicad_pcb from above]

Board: 2 copper layers, 100.0 x 100.0 mm, 114 parts (0 on the bottom side), 29 nets.

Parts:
J1, J2: Conn_01x02_Male; 2pin_tight
J3: Conn_01x05_Male; 5pin_tight
J4, J5, J6, J7: Conn_01x04_Male; 4pin_tight
J15: Conn_01x03_Male; 3hardware_selector
Q1, Q2, Q3, Q4, Q5, Q6, Q7, Q8, Q9, Q10, Q11, Q12, Q13, Q14, Q15, Q16, Q17, Q18, Q19, Q20, Q21, Q22, Q23, Q24, Q25, Q26, Q27, Q28, Q29, Q30, Q31, Q32, Q33, Q34, Q35, Q36, Q37, Q38, Q39, Q40, Q41, Q42, Q43, Q44, Q45, Q46, Q47, Q48, Q49, Q50, Q51, Q52, Q53, Q54, Q55, Q56, Q57, Q58, Q59, Q60, Q61, Q62, Q63, Q64, Q65, Q66, Q67, Q68, Q69, Q70, Q71, Q72, Q73, Q74, Q75, Q76, Q77, Q78, Q79, Q80, Q81, Q82, Q83, Q84, Q85: 2N7000; 2n7000_tight
R1, R2, R3, R4, R5, R6, R7, R8, R9, R10, R11, R12, R13, R14, R15, R16, R17, R18, R19, R20, R21: R; resistor_tight

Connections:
+5V: J1.1, J2.1, R1.1, R2.1, R3.1, R4.1, R5.1, R6.1, R7.1, R8.1, R9.1, R10.1, R11.1, R12.1, R13.1, R14.1, R15.1, R16.1, R17.1, R18.1, R19.1, R20.1, R21.1
/Sheet63BAD094/out: J4.4, Q1.3, Q2.3, Q3.3, Q4.3, Q5.3, R1.2
/Sheet63C0593F/a: J3.5, J15.1, Q85.2
/Sheet63C0593F/na: J15.3, Q85.3, R21.2
/asel: J15.2, Q1.2, Q6.2, Q11.2, Q16.2, Q21.2, Q26.2, Q31.2, Q36.2, Q41.2, Q46.2, Q51.2, Q56.2, Q61.2, Q66.2, Q71.2, Q76.2
/b: J3.4, Q42.2, Q47.2, Q52.2, Q57.2, Q62.2, Q67.2, Q72.2, Q77.2, Q81.2
/c: J3.3, Q23.2, Q28.2, Q33.2, Q38.2, Q63.2, Q68.2, Q73.2, Q78.2, Q82.2
/d: J3.2, Q14.2, Q19.2, Q34.2, Q39.2, Q54.2, Q59.2, Q74.2, Q79.2, Q83.2
/e: J3.1, Q10.2, Q20.2, Q30.2, Q40.2, Q50.2, Q60.2, Q70.2, Q80.2, Q84.2
/nb: Q2.2, Q7.2, Q12.2, Q17.2, Q22.2, Q27.2, Q32.2, Q37.2, Q81.3, R17.2
/nc: Q3.2, Q8.2, Q13.2, Q18.2, Q43.2, Q48.2, Q53.2, Q58.2, Q82.3, R18.2
/nd: Q4.2, Q9.2, Q24.2, Q29.2, Q44.2, Q49.2, Q64.2, Q69.2, Q83.3, R19.2
/ne: Q5.2, Q15.2, Q25.2, Q35.2, Q45.2, Q55.2, Q65.2, Q75.2, Q84.3, R20.2
/sheet63BC13F1/out: J4.3, Q6.3, Q7.3, Q8.3, Q9.3, Q10.3, R2.2
/sheet63BC40A0/out: J5.3, Q26.3, Q27.3, Q28.3, Q29.3, Q30.3, R6.2
/sheet63BC40A1/out: J5.2, Q31.3, Q32.3, Q33.3, Q34.3, Q35.3, R7.2
/sheet63BC40A2/out: J5.1, Q36.3, Q37.3, Q38.3, Q39.3, Q40.3, R8.2
/sheet63BC409F/out: J5.4, Q21.3, Q22.3, Q23.3, Q24.3, Q25.3, R5.2
/sheet63BC745C/out: J6.4, Q41.3, Q42.3, Q43.3, Q44.3, Q45.3, R9.2
/sheet63BC745D/out: J6.3, Q46.3, Q47.3, Q48.3, Q49.3, Q50.3, R10.2
/sheet63BC745E/out: J6.2, Q51.3, Q52.3, Q53.3, Q54.3, Q55.3, R11.2
/sheet63BC745F/out: J6.1, Q56.3, Q57.3, Q58.3, Q59.3, Q60.3, R12.2
/sheet63BC2018/out: J4.2, Q11.3, Q12.3, Q13.3, Q14.3, Q15.3, R3.2
/sheet63BC2019/out: J4.1, Q16.3, Q17.3, Q18.3, Q19.3, Q20.3, R4.2
/sheet63BC7460/out: J7.4, Q61.3, Q62.3, Q63.3, Q64.3, Q65.3, R13.2
/sheet63BC7461/out: J7.3, Q66.3, Q67.3, Q68.3, Q69.3, Q70.3, R14.2
/sheet63BC7462/out: J7.2, Q71.3, Q72.3, Q73.3, Q74.3, Q75.3, R15.2
/sheet63BC7463/out: J7.1, Q76.3, Q77.3, Q78.3, Q79.3, Q80.3, R16.2
GND: J1.2, J2.2, Q1.1, Q2.1, Q3.1, Q4.1, Q5.1, Q6.1, Q7.1, Q8.1, Q9.1, Q10.1, Q11.1, Q12.1, Q13.1, Q14.1, Q15.1, Q16.1, Q17.1, Q18.1, Q19.1, Q20.1, Q21.1, Q22.1, Q23.1, Q24.1, Q25.1, Q26.1, Q27.1, Q28.1, Q29.1, Q30.1, Q31.1, Q32.1, Q33.1, Q34.1, Q35.1, Q36.1, Q37.1, Q38.1, Q39.1, Q40.1, Q41.1, Q42.1, Q43.1, Q44.1, Q45.1, Q46.1, Q47.1, Q48.1, Q49.1, Q50.1, Q51.1, Q52.1, Q53.1, Q54.1, Q55.1, Q56.1, Q57.1, Q58.1, Q59.1, Q60.1, Q61.1, Q62.1, Q63.1, Q64.1, Q65.1, Q66.1, Q67.1, Q68.1, Q69.1, Q70.1, Q71.1, Q72.1, Q73.1, Q74.1, Q75.1, Q76.1, Q77.1, Q78.1, Q79.1, Q80.1, Q81.1, Q82.1, Q83.1, Q84.1, Q85.1
